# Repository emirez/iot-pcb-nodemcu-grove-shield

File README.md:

# iot-pcb-esp32-eagle-v2
NodeMCU Grove Shield Design from ThingForward.io

See [ESP32 DevKitC - PCB Design Story Blog Post](https://www.thingforward.io/index.php?id=107)

# License
This work is licensed under a [Creative Commons Attribution-ShareAlike 4.0 International License](https://creativecommons.org/licenses/by-sa/4.0/).

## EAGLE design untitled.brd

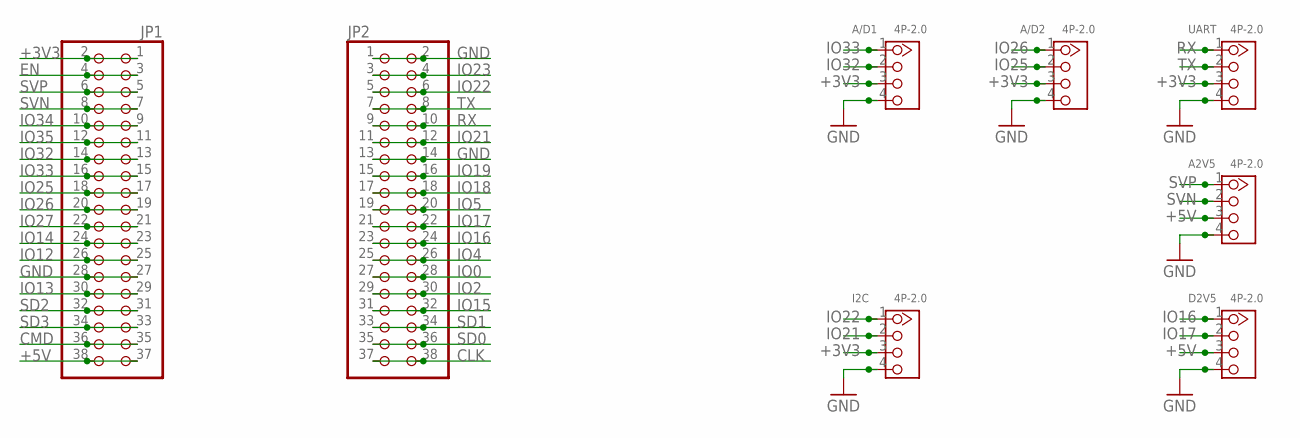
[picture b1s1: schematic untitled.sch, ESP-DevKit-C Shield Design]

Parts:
A2V5: 4P-2.0; HW4-2.0
A/D1, A/D2: 4P-2.0; HW4-2.0
D2V5: 4P-2.0; HW4-2.0
I2C: 4P-2.0; HW4-2.0
JP1, JP2: PINHD-2X19; 2X19
UART: 4P-2.0; HW4-2.0

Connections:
+3V3: A/D1.3, A/D2.3, I2C.3, JP1.1, JP1.2, UART.3
+5V: A2V5.3, D2V5.3, JP1.37, JP1.38
CLK: JP2.37, JP2.38
CMD: JP1.35, JP1.36
EN: JP1.3, JP1.4
GND: A2V5.4, A/D1.4, A/D2.4, D2V5.4, I2C.4, JP1.27, JP1.28, JP2.1, JP2.2, JP2.13, JP2.14, UART.4
IO0: JP2.27, JP2.28
IO2: JP2.29, JP2.30
IO4: JP2.25, JP2.26
IO5: JP2.19, JP2.20
IO12: JP1.25, JP1.26
IO13: JP1.29, JP1.30
IO14: JP1.23, JP1.24
IO15: JP2.31, JP2.32
IO16: D2V5.1, JP2.23, JP2.24
IO17: D2V5.2, JP2.21, JP2.22
IO18: JP2.17, JP2.18
IO19: JP2.15, JP2.16
IO21: I2C.2, JP2.11, JP2.12
IO22: I2C.1, JP2.5, JP2.6
IO23: JP2.3, JP2.4
IO25: A/D2.2, JP1.17, JP1.18
IO26: A/D2.1, JP1.19, JP1.20
IO27: JP1.21, JP1.22
IO32: A/D1.2, JP1.13, JP1.14
IO33: A/D1.1, JP1.15, JP1.16
IO34: JP1.9, JP1.10
IO35: JP1.11, JP1.12
RX: JP2.9, JP2.10, UART.1
SD0: JP2.35, JP2.36
SD1: JP2.33, JP2.34
SD2: JP1.31, JP1.32
SD3: JP1.33, JP1.34
SVN: A2V5.2, JP1.7, JP1.8
SVP: A2V5.1, JP1.5, JP1.6
TX: JP2.7, JP2.8, UART.2

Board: 2 copper layers, 9 parts (0 on the bottom side), 36 nets, no tracks yet.

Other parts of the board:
U$5: BREADBOARD_SPACING

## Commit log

2018-10-04 new repo ok

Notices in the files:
parts and their libraries:
SparkFun-Aesthetics: Licensing: Creative Commons ShareAlike 4.0 International - https://creativecommons.org/licenses/by-sa/4.0
